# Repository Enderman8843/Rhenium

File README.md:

# Rhenium 
It is a Keyboard that is powered by RP2040 microprocessor that uses a USB-C, this keyboard is using akko v3 pro black switches also this has a layout of a slight variation of ANSI-104 

### Demo : https://drive.google.com/file/d/1mEruNO0NkJvDSLDQcf2VO9Js_aKwS2UY/view?usp=sharing
### Demo : https://drive.google.com/file/d/1Fq-R3P4Wu6ONQhNlfD0M-4PFkLKanZj8/view
# Photos

# KMK FIRMWARE 
*ALWAYS USE THIS
1. Install CircuitPY
2. Copy these files: -https://github.com/Enderman8843/Rhenium/tree/f9bf0482101a7b040eca7897d7e98482e09b73b1/firmware/KMK%20FIRMWARE

# QMK FIRMWARE 
*Bit Glitchy 
1. Put this UF2 in rpi
https://github.com/Enderman8843/Rhenium/tree/909fbee6c6720d5a931a36db898d5d94f6ce02c9/firmware/UF2FILES/QMK

## Why Rhenium?
Personally I had never used a mechanical keyboard in my life and only relied on cheap membrane keyboard or use my laptop's keyboard , But when I heard about Blueprint I decided to change it all at once and build myself a Mechanical keyboard , And also decided that I need to have everything custom nothing extrenal thus I embeded the microprocessor into the pcb making it better!

Rhenium was named after the inspiration taken from the chromium browser!

## How To Use ?
To use this computer appartus I would suggest using your biological input device so called digits i.e. fingers ,Begin by selecting finger of your choice then elevate your finger about 0.3-0.4 cm above the desired key then place it in on that particular key then gently apply 0.30N of magnitude of force this would lead your visual display unit to render the desired character represented by the key , Simple as that

Before that make sure the assemeble the keyboard and connect it via the usb-c , and to flash the firmware use the bootsel btn and read the above for both KMK and QMK
## Case Render

| Top & Side View | Rear view |
|----------------|-------------------|
|  |  |

| Full Assembly View |
|-------------------|
|  |

---

## PCB Layout and Render

| PCB  | Schematics /Wiring |
|-------------|----------------|
|  | |
| 3D view |
|-------------------|
|||

## JLCPCB ORDER 

## Shipment Option 

See I did not find gdsr option so I chose UPS world wide express shipment

## BOM
| Item | Description | Quantity | Unit Price ($) | Total Price ($) | URL |
|------|------------|----------|----------------|-----------------|-----|
| PCB | JLCPCB | 1 | 113.66 | 113.66 | https://jlcpcb.com |
| Pinecil V2 | Solder Iron | 1 | OWNED | 0.00 | OWNED |
| Diodes | Diodes | 75 | 0.01 | 1 | Owned |
| Case | Print Legion Shipment | 1 | 6.00 | 6.00 | https://hackclub.com |
| Akko Switches | Switch Set (45) | 2 | 14.00 | 28.00 | https://stackskb.com/store/akko-v3-cream-black-pro-switch-pack-of-45/ |
| Keycaps | MDA Profile Keycaps | 1 | 16.69 | 16.69 | https://stackskb.com/store/stackspbt-lavender-mda-profile-keycaps-131-key/ |
| OLED Display | 0.91" OLED Display | 1 | 2.23 | 2.23 | https://robu.in/product/blue-oled-display-module/ |
| Vertical Rotary Encoder | Rotary Encoder | 1 | 2.00 | 2.00 | https://www.amazon.in/dp/B0888RWNM1 |
| Rotary Cap | Knob Cap | 1 | 0.40 | 0.40 | https://robu.in/product/potentiometer-knob-rotary-switch-cap-black-color-pack-of-5-pcs/ |
| M2 Screw + Hex + Washer | Misc Hardware | 6 | 0.80 | 0.80 | https://onlyscrews.in/products/m2-nut-ss-304 |
| Soldering Essentials | Solder+Flux+TipCleaner | 1 | 4.54 | 4.54 | https://robocraze.com/products/7cmx5-5cm-soldering-cleaning-sponge-for-soldering-irons-work-stands?variant=47303371227360 , https://robu.in/product/solder-wire-0-8mm50g/ , https://robu.in/product/noel-flux-soldering-paste-10g/ |
| **TOTAL** |  |  |  | **175 $** |  |

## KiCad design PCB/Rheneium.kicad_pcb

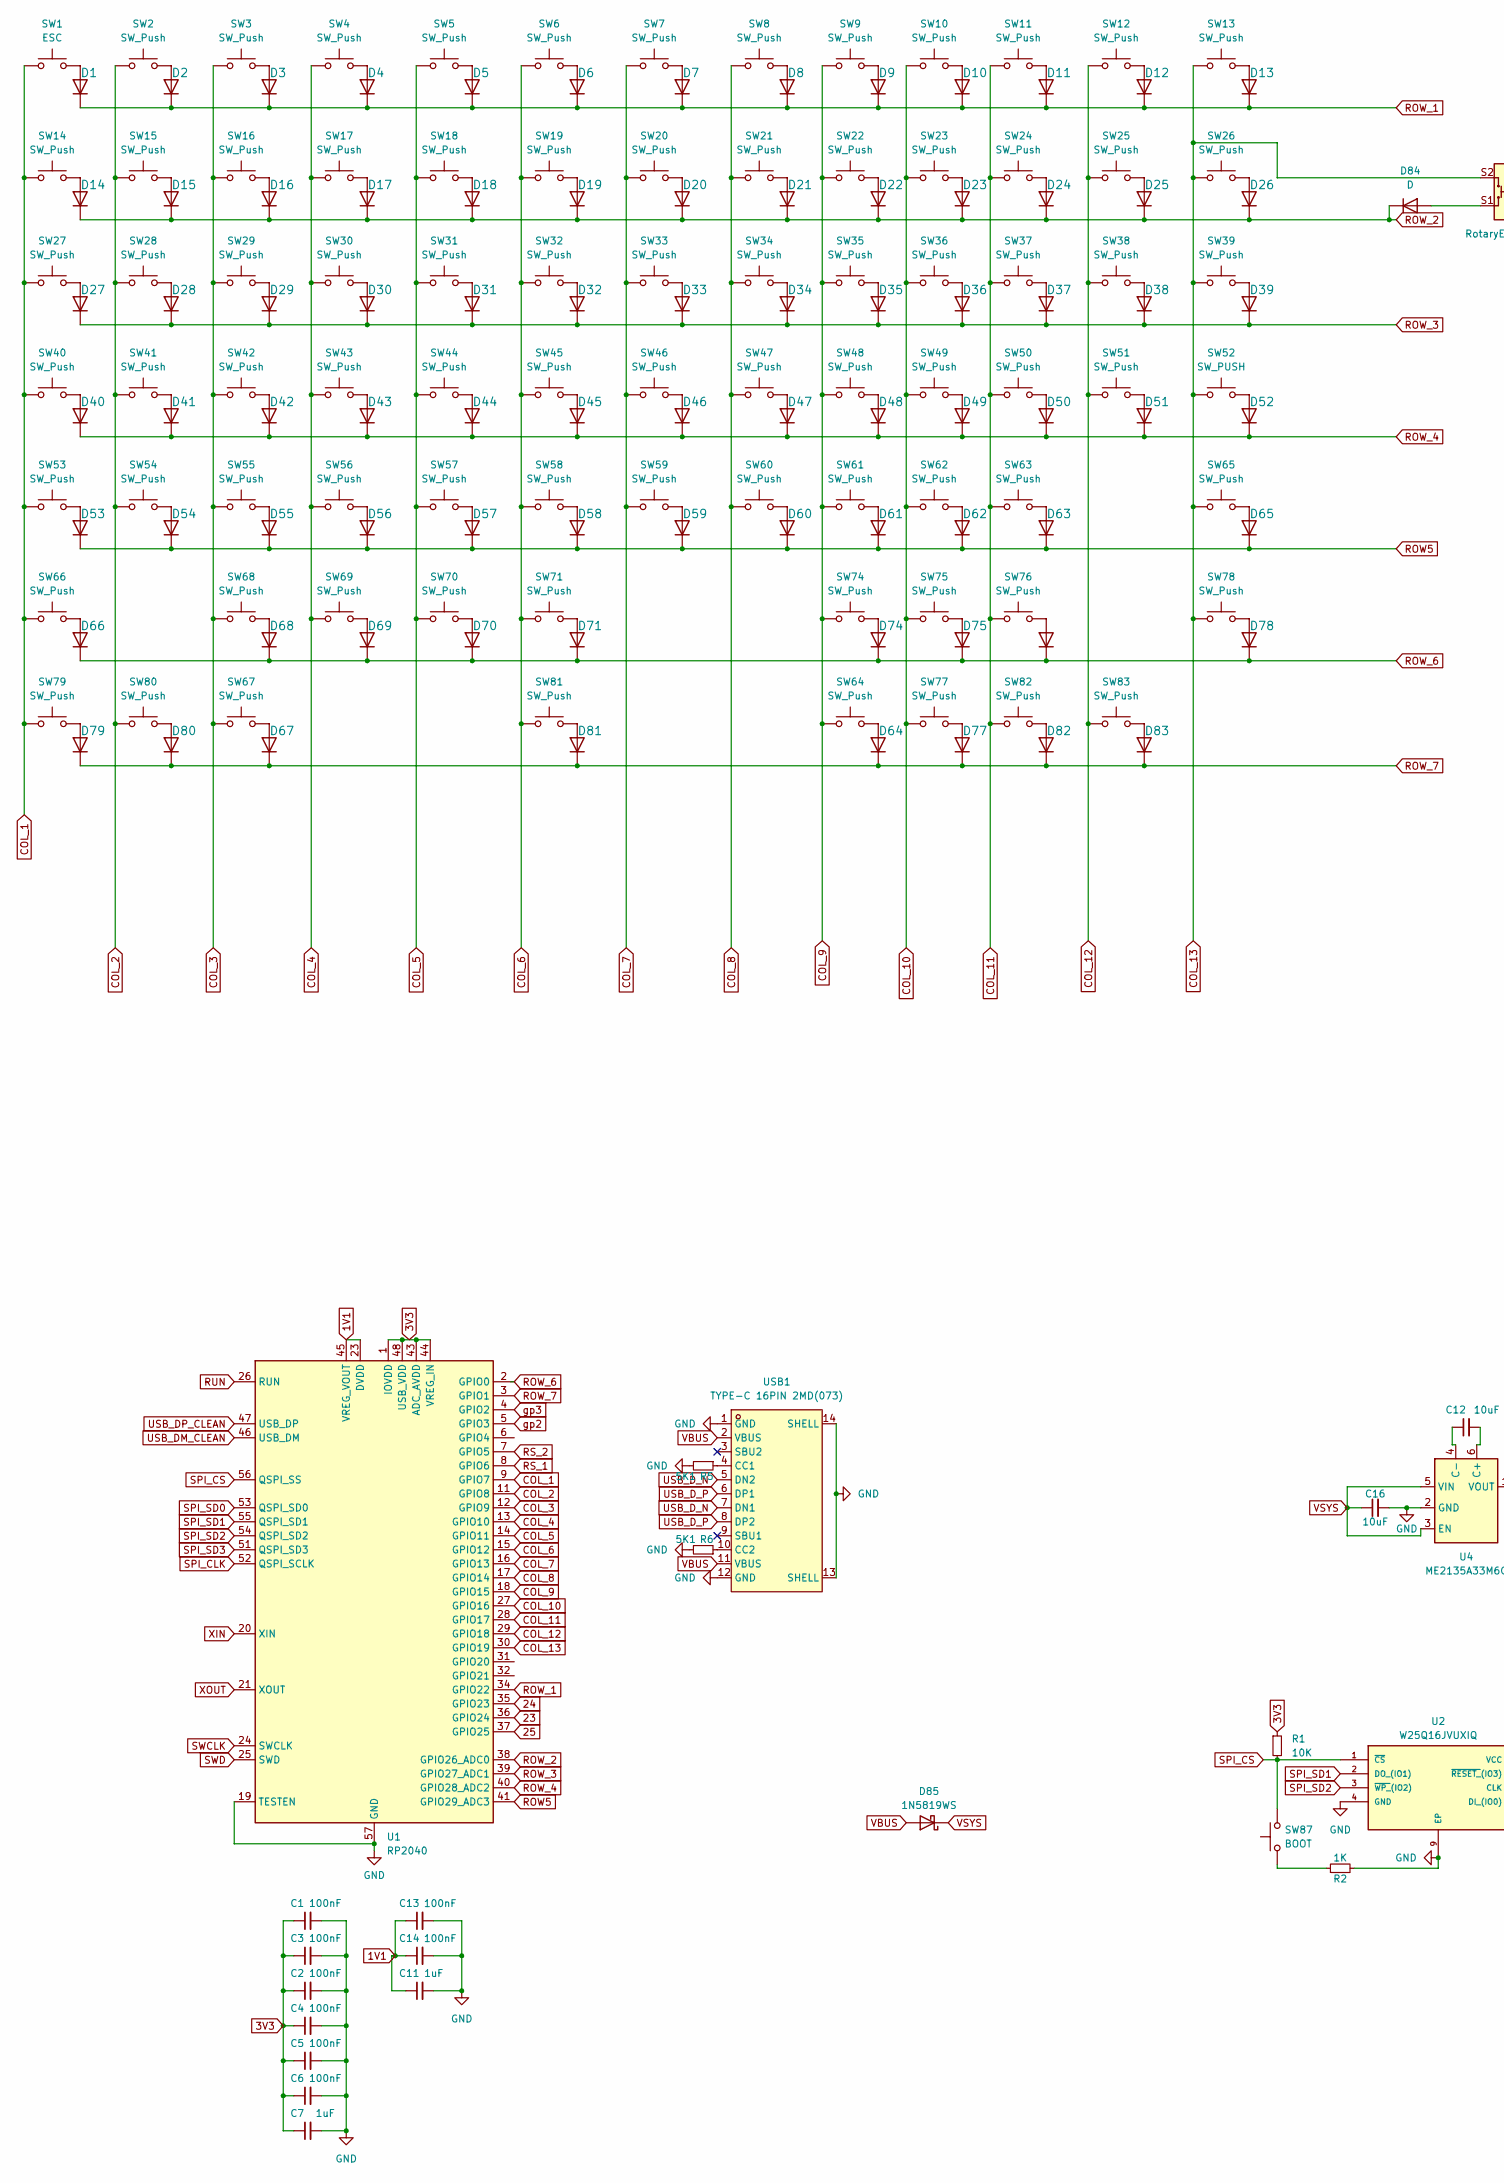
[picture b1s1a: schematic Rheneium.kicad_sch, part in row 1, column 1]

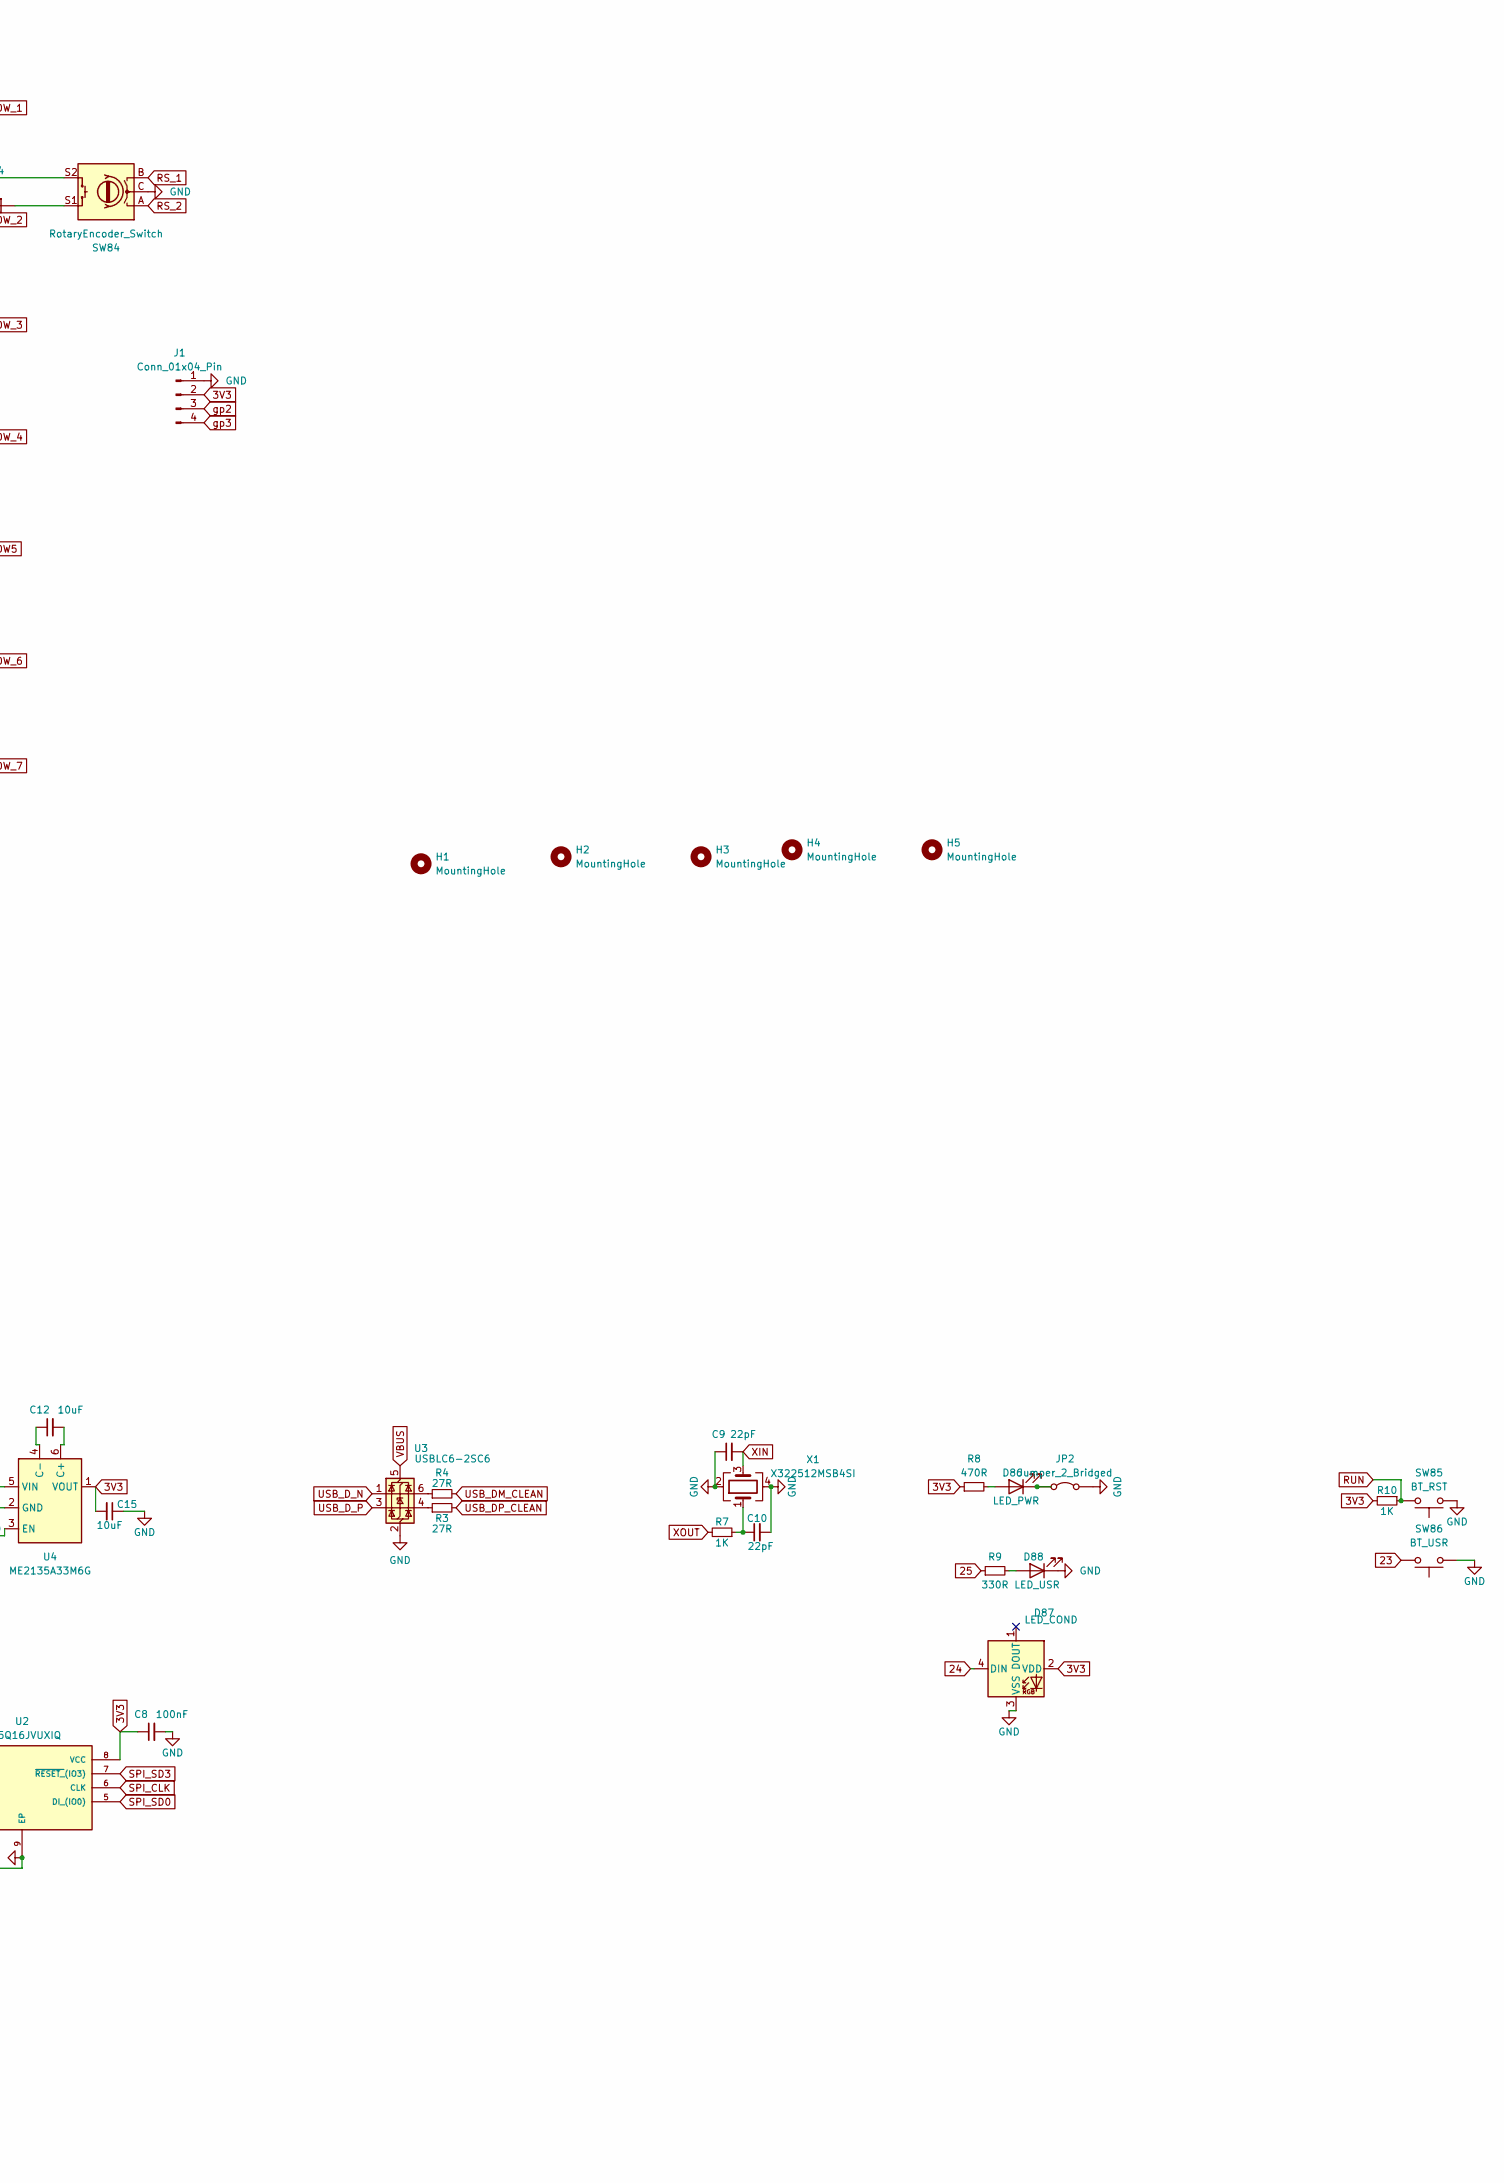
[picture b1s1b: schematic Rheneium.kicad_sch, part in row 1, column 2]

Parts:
C1, C2, C3, C4, C5, C6, C8, C13, C14: 100nF; C_0402_1005Metric
C7, C11: 1uF; C_0402_1005Metric
C9, C10: 22pF; C_0402_1005Metric
C12: 10uF; C_0805_2012Metric
C15, C16: 10uF; C_0402_1005Metric
D1, D2, D3, D4, D5, D6, D7, D8, D9, D10, D11, D12, D13, D14, D15, D16, D17, D18, D19, D20, D21, D22, D23, D24, D25, D26, D27, D28, D29, D30, D31, D32, D33, D34, D35, D36, D37, D38, D39, D40, D41, D42, D43, D44, D45, D46, D47, D48, D49, D50, D51, D52, D53, D54, D55, D56, D57, D58, D59, D60, D61, D62, D63, D64, D65, D66, D67, D68, D69, D70, D71, D74, D75, D76, D77, D78, D79, D80, D81, D82, D83, D84: D; D_0805_2012Metric_Pad1.15x1.40mm_HandSolder
D85: 1N5819WS; D_SOD-323
D86: LED_PWR; LED_0603_1608Metric
D87: LED_COND; LED_SK6812MINI_PLCC4_3.5x3.5mm_P1.75mm
D88: LED_USR; LED_0603_1608Metric
H1, H2, H3, H4, H5: MountingHole; MountingHole_2.2mm_M2
J1: Conn_01x04_Pin; SSD1306-0.91-OLED-4pin-128x32
JP2: Jumper_2_Bridged; SolderJumper-2_P1.3mm_Bridged2Bar_RoundedPad1.0x1.5mm
R1: 10K; R_0402_1005Metric
R2, R7, R10: 1K; R_0402_1005Metric
R3, R4: 27R; R_0402_1005Metric
R5, R6: 5K1; R_0402_1005Metric
R8: 470R; R_0402_1005Metric
R9: 330R; R_0402_1005Metric
SW1: ESC; SW_Cherry_MX_1.00u_PCB
SW2, SW3, SW4, SW5, SW6, SW7, SW8, SW9, SW10, SW11, SW12, SW13, SW14, SW15, SW16, SW17, SW18, SW19, SW20, SW21, SW22, SW23, SW24, SW25, SW28, SW29, SW30, SW31, SW32, SW33, SW34, SW35, SW36, SW37, SW38, SW41, SW42, SW43, SW44, SW45, SW46, SW47, SW48, SW49, SW50, SW51, SW54, SW55, SW56, SW57, SW58, SW59, SW60, SW61, SW62, SW63, SW66, SW68, SW69, SW70, SW71, SW74, SW75, SW76, SW78: SW_Push; SW_Cherry_MX_1.00u_PCB
SW26: SW_Push; SW_Cherry_MX_2.00u_PCB
SW27, SW39: SW_Push; SW_Cherry_MX_1.50u_PCB
SW40: SW_Push; SW_Cherry_MX_1.75u_PCB
SW52: SW_PUSH; SW_Cherry_MX_2.25u_PCB
SW53: SW_Push; SW_Cherry_MX_2.25u_PCB
SW64, SW67, SW77, SW79, SW80, SW82, SW83: SW_Push; SW_Cherry_MX_1.25u_PCB
SW65: SW_Push; SW_Cherry_MX_2.75u_PCB
SW81: SW_Push; SW_Cherry_MX_6.25u_PCB
SW84: RotaryEncoder_Switch; RotaryEncoder_Alps_EC11E-Switch_Vertical_H20mm
SW85: BT_RST; SW_Push_1P1T_NO_CK_KMR2
SW86: BT_USR; SW_Push_1P1T_NO_CK_KMR2
SW87: BOOT; SW_Push_1P1T_NO_CK_KMR2
U1: RP2040; QFN-56-1EP_7x7mm_P0.4mm_EP3.2x3.2mm
U2: W25Q16JVUXIQ; Winbond_USON-8-1EP_3x2mm_P0.5mm_EP0.2x1.6mm; MANUFACTURER_PART_NUMBER W25Q16JVUXIQ; LCSC C2843335
U3: USBLC6-2SC6; SOT-23-6
U4: ME2135A33M6G; SOT-23-6; LCSC C610271
USB1: TYPE-C 16PIN 2MD(073); USB-C-SMD_TYPE-C-6PIN-2MD-073; LCSC Part C2765186
X1: X322512MSB4SI; Crystal_SMD_3225-4Pin_3.2x2.5mm; LCSC C9002

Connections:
1V1: C11.1, C13.1, C14.1, U1.23 (DVDD), U1.45 (VREG_VOUT), U1.50 (DVDD)
3V3: C1.1, C2.1, C3.1, C4.1, C5.1, C6.1, C7.1, C8.1, C15.2, D87.2 (VDD), J1.2, R1.1, R8.1, R10.2, U1.1 (IOVDD), U1.10 (IOVDD), U1.22 (IOVDD), U1.33 (IOVDD), U1.42 (IOVDD), U1.43 (ADC_AVDD), U1.44 (VREG_IN), U1.48 (USB_VDD), U1.49 (IOVDD), U2.8 (VCC), U4.1 (VOUT)
23: SW86.2, U1.36 (GPIO24)
24: D87.4 (DIN), U1.35 (GPIO23)
25: R9.1, U1.37 (GPIO25)
COL_1: SW1.1, SW14.1, SW27.1, SW40.1, SW53.1, SW66.1, SW79.1, U1.9 (GPIO7)
COL_2: SW2.1, SW15.1, SW28.1, SW41.1, SW54.1, SW80.1, U1.11 (GPIO8)
COL_3: SW3.1, SW16.1, SW29.1, SW42.1, SW55.1, SW67.1, SW68.1, U1.12 (GPIO9)
COL_4: SW4.1, SW17.1, SW30.1, SW43.1, SW56.1, SW69.1, U1.13 (GPIO10)
COL_5: SW5.1, SW18.1, SW31.1, SW44.1, SW57.1, SW70.1, U1.14 (GPIO11)
COL_6: SW6.1, SW19.1, SW32.1, SW45.1, SW58.1, SW71.1, SW81.1, U1.15 (GPIO12)
COL_7: SW7.1, SW20.1, SW33.1, SW46.1, SW59.1, U1.16 (GPIO13)
COL_8: SW8.1, SW21.1, SW34.1, SW47.1, SW60.1, U1.17 (GPIO14)
COL_9: SW9.1, SW22.1, SW35.1, SW48.1, SW61.1, SW64.1, SW74.1, U1.18 (GPIO15)
COL_10: SW10.1, SW23.1, SW36.1, SW49.1, SW62.1, SW75.1, SW77.1, U1.27 (GPIO16)
COL_11: SW11.1, SW24.1, SW37.1, SW50.1, SW63.1, SW76.1, SW82.1, U1.28 (GPIO17)
COL_12: SW12.1, SW25.1, SW38.1, SW51.1, SW83.1, U1.29 (GPIO18)
COL_13: SW13.1, SW26.1, SW39.1, SW52.1, SW65.1, SW78.1, SW84.S2, U1.30 (GPIO19)
GND: C1.2, C2.2, C3.2, C4.2, C5.2, C6.2, C7.2, C8.2, C9.1, C10.2, C11.2, C13.2, C14.2, C15.1, C16.2, D87.3 (VSS), D88.1 (K), J1.1, JP2.2 (B), R2.2, R5.2, R6.2, SW84.C, SW85.1, SW86.1, U1.19 (TESTEN), U1.57 (GND), U2.4 (GND), U2.9 (EP), U3.2 (GND), U4.2 (GND), USB1.1 (GND), USB1.12 (GND), USB1.13 (SHELL), USB1.14 (SHELL), X1.2, X1.4
unnamed: C10.1, R7.1, X1.1
unnamed: D1.2 (A), SW1.2
unnamed: D2.2 (A), SW2.2
unnamed: D3.2 (A), SW3.2
unnamed: D4.2 (A), SW4.2
unnamed: D5.2 (A), SW5.2
unnamed: D6.2 (A), SW6.2
unnamed: D7.2 (A), SW7.2
unnamed: D8.2 (A), SW8.2
unnamed: D9.2 (A), SW9.2
unnamed: D10.2 (A), SW10.2
unnamed: D11.2 (A), SW11.2
unnamed: D12.2 (A), SW12.2
unnamed: D13.2 (A), SW13.2
unnamed: D14.2 (A), SW14.2
unnamed: D15.2 (A), SW15.2
unnamed: D16.2 (A), SW16.2
unnamed: D17.2 (A), SW17.2
unnamed: D18.2 (A), SW18.2
unnamed: D19.2 (A), SW19.2
unnamed: D20.2 (A), SW20.2
unnamed: D21.2 (A), SW21.2
unnamed: D22.2 (A), SW22.2
unnamed: D23.2 (A), SW23.2
unnamed: D24.2 (A), SW24.2
unnamed: D25.2 (A), SW25.2
unnamed: D26.2 (A), SW26.2
unnamed: D27.2 (A), SW27.2
unnamed: D28.2 (A), SW28.2
unnamed: D29.2 (A), SW29.2
unnamed: D30.2 (A), SW30.2
unnamed: D31.2 (A), SW31.2
unnamed: D32.2 (A), SW32.2
unnamed: D33.2 (A), SW33.2
unnamed: D34.2 (A), SW34.2
unnamed: D35.2 (A), SW35.2
unnamed: D36.2 (A), SW36.2
unnamed: D37.2 (A), SW37.2
unnamed: D38.2 (A), SW38.2
unnamed: D39.2 (A), SW39.2
unnamed: D40.2 (A), SW40.2
unnamed: D41.2 (A), SW41.2
unnamed: D42.2 (A), SW42.2
unnamed: D43.2 (A), SW43.2
unnamed: D44.2 (A), SW44.2
unnamed: D45.2 (A), SW45.2
unnamed: D46.2 (A), SW46.2
unnamed: D47.2 (A), SW47.2
unnamed: D48.2 (A), SW48.2
unnamed: D49.2 (A), SW49.2
unnamed: D50.2 (A), SW50.2
unnamed: D51.2 (A), SW51.2
unnamed: D52.2 (A), SW52.2
unnamed: D53.2 (A), SW53.2
unnamed: D54.2 (A), SW54.2
unnamed: D55.2 (A), SW55.2
unnamed: D56.2 (A), SW56.2
unnamed: D57.2 (A), SW57.2
unnamed: D58.2 (A), SW58.2
unnamed: D59.2 (A), SW59.2
unnamed: D60.2 (A), SW60.2
unnamed: D61.2 (A), SW61.2
unnamed: D62.2 (A), SW62.2
unnamed: D63.2 (A), SW63.2
unnamed: D64.2 (A), SW64.2
unnamed: D65.2 (A), SW65.2
unnamed: D66.2 (A), SW66.2
unnamed: D67.2 (A), SW67.2
unnamed: D68.2 (A), SW68.2
unnamed: D69.2 (A), SW69.2
unnamed: D70.2 (A), SW70.2
unnamed: D71.2 (A), SW71.2
unnamed: D74.2 (A), SW74.2
unnamed: D75.2 (A), SW75.2
unnamed: D76.2 (A), SW76.2
unnamed: D77.2 (A), SW77.2
unnamed: D78.2 (A), SW78.2
unnamed: D79.2 (A), SW79.2
unnamed: D80.2 (A), SW80.2
unnamed: D81.2 (A), SW81.2
unnamed: D82.2 (A), SW82.2
unnamed: D83.2 (A), SW83.2
unnamed: D84.2 (A), SW84.S1
unnamed: D86.2 (A), R8.2
unnamed: D86.1 (K), JP2.1 (A)
unnamed: D88.2 (A), R9.2
unnamed: R2.1, SW87.1
unnamed: R3.1, U3.4 (I/O2)
unnamed: R4.1, U3.6 (I/O1)
unnamed: C12.2, U4.6 (C+)
unnamed: C12.1, U4.4 (C-)
unnamed: R5.1, USB1.4 (CC1)
unnamed: R6.1, USB1.10 (CC2)
ROW5: D53.1 (K), D54.1 (K), D55.1 (K), D56.1 (K), D57.1 (K), D58.1 (K), D59.1 (K), D60.1 (K), D61.1 (K), D62.1 (K), D63.1 (K), D65.1 (K), U1.41 (GPIO29_ADC3)
ROW_1: D1.1 (K), D2.1 (K), D3.1 (K), D4.1 (K), D5.1 (K), D6.1 (K), D7.1 (K), D8.1 (K), D9.1 (K), D10.1 (K), D11.1 (K), D12.1 (K), D13.1 (K), U1.34 (GPIO22)
ROW_2: D14.1 (K), D15.1 (K), D16.1 (K), D17.1 (K), D18.1 (K), D19.1 (K), D20.1 (K), D21.1 (K), D22.1 (K), D23.1 (K), D24.1 (K), D25.1 (K), D26.1 (K), D84.1 (K), U1.38 (GPIO26_ADC0)
ROW_3: D27.1 (K), D28.1 (K), D29.1 (K), D30.1 (K), D31.1 (K), D32.1 (K), D33.1 (K), D34.1 (K), D35.1 (K), D36.1 (K), D37.1 (K), D38.1 (K), D39.1 (K), U1.39 (GPIO27_ADC1)
ROW_4: D40.1 (K), D41.1 (K), D42.1 (K), D43.1 (K), D44.1 (K), D45.1 (K), D46.1 (K), D47.1 (K), D48.1 (K), D49.1 (K), D50.1 (K), D51.1 (K), D52.1 (K), U1.40 (GPIO28_ADC2)
ROW_6: D66.1 (K), D68.1 (K), D69.1 (K), D70.1 (K), D71.1 (K), D74.1 (K), D75.1 (K), D76.1 (K), D78.1 (K), U1.2 (GPIO0)
ROW_7: D64.1 (K), D67.1 (K), D77.1 (K), D79.1 (K), D80.1 (K), D81.1 (K), D82.1 (K), D83.1 (K), U1.3 (GPIO1)
RS_1: SW84.B, U1.8 (GPIO6)
RS_2: SW84.A, U1.7 (GPIO5)
RUN: R10.1, SW85.2, U1.26 (RUN)
SPI_CLK: U1.52 (QSPI_SCLK), U2.6 (CLK)
SPI_CS: R1.2, SW87.2, U1.56 (QSPI_SS), U2.1 (~CS)
SPI_SD0: U1.53 (QSPI_SD0), U2.5 (DI_(IO0))
SPI_SD1: U1.55 (QSPI_SD1), U2.2 (DO_(IO1))
SPI_SD2: U1.54 (QSPI_SD2), U2.3 (~WP_(IO2))
SPI_SD3: U1.51 (QSPI_SD3), U2.7 (~RESET_(IO3))
SWCLK: U1.24 (SWCLK)
SWD: U1.25 (SWD)
USB_DM_CLEAN: R4.2, U1.46 (USB_DM)
USB_DP_CLEAN: R3.2, U1.47 (USB_DP)
USB_D_N: U3.1 (I/O1), USB1.5 (DN2), USB1.7 (DN1)
USB_D_P: U3.3 (I/O2), USB1.6 (DP1), USB1.8 (DP2)
VBUS: D85.2 (A), U3.5 (VBUS), USB1.2 (VBUS), USB1.11 (VBUS)
VSYS: C16.1, D85.1 (K), U4.3 (EN), U4.5 (VIN)
XIN: C9.2, U1.20 (XIN), X1.3
XOUT: R7.2, U1.21 (XOUT)
gp2: J1.3, U1.5 (GPIO3)
gp3: J1.4, U1.4 (GPIO2)

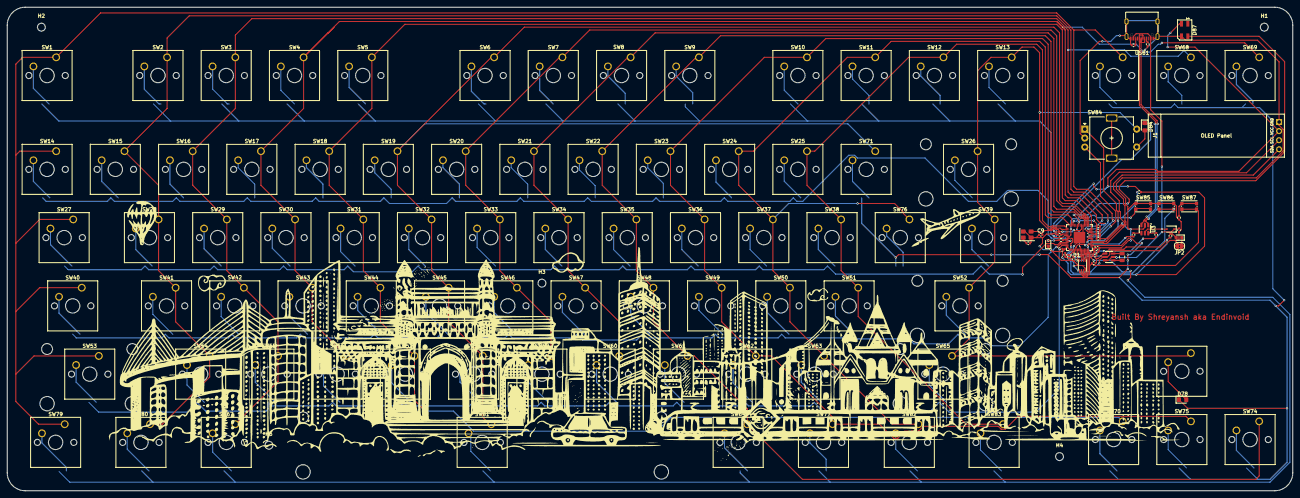
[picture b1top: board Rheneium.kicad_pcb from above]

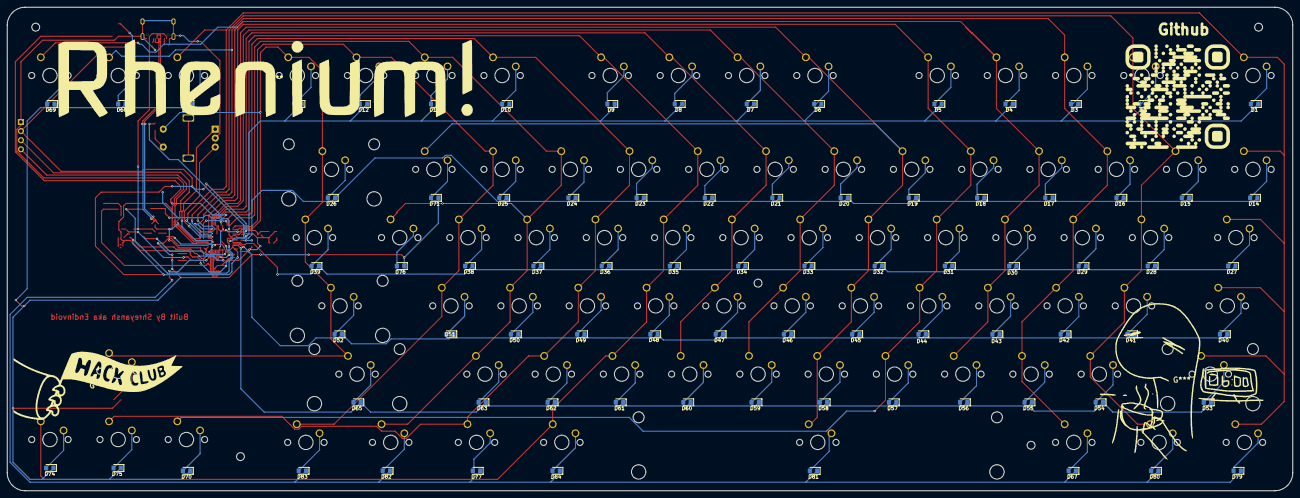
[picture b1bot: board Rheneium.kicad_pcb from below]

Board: 2 copper layers, 358.8 x 134.9 mm, 209 parts (80 on the bottom side), 137 nets.

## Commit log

2025-12-25 Created PCB folder
2025-12-25 Create cas
2025-12-25 Added firmware.py
2025-12-25 Create README.md with project details and images
    Added initial project description and images.
2025-12-26 Enhance Rhenium keyboard description in README
    Expanded the description of the Rhenium keyboard to include details about its microprocessor, connection type, switch compatibility, and layout.
2025-12-29 Added BOM
2025-12-31 Update PCB layout image in README
2026-01-02 did nothing
2026-01-06 Create pcbfiles
2026-01-06 Renamed
2026-01-06 Add production file to Production directory
2026-01-06 Create spe
2026-01-06 Create price
2026-01-06 Add BOM section to README
    Added Bill of Materials (BOM) section with item details.
2026-01-15 PLSSSSSSSSSSSSSSS
2026-01-20 Fix spelling and grammar in README.md
    Corrected spelling errors and improved clarity in the README.
2026-02-17 Refactor PCB layout images in README
2026-02-18 Revise images and layout in README
    Updated images and formatting in README.md.
2026-02-18 Fix formatting and layout in README.md
2026-02-18 Create casetemp
2026-02-19 Rename case/RheniumCADNew.step to Rhenium_Full.step
2026-02-19 Create case
2026-02-27 Minor Changes
2026-03-05 Update Schematics section in README
2026-03-05 Add diodes entry to the components table
2026-03-05 Fix typo in README description of keyboard
    Corrected a typo in the description of the keyboard's microprocessor.
2026-03-06 added to as
2026-03-18 Update PCB description in BOM table
2026-04-17 FINALLLY
2026-04-17 final
2026-04-17 adsads
    ddsda
2026-04-17 sadsa
